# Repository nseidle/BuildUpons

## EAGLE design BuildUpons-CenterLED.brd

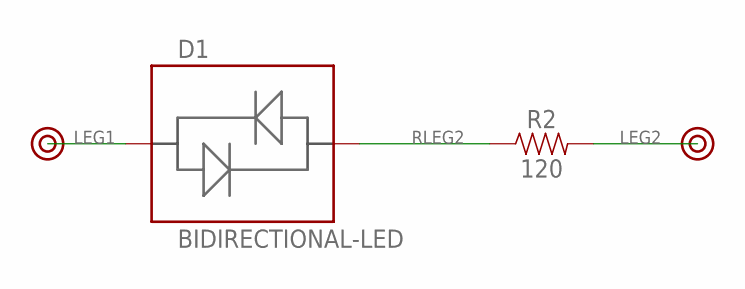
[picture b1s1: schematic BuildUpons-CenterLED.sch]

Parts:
D1: BIDIRECTIONAL-LED
J1, J2: METAL-LEGMOREPASTE; METAL-LEG
R2: 120; 0402

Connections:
LEG1: D1.LED1, J1.1
LEG2: J2.1, R2.2
RLEG2: D1.LED2, R2.1

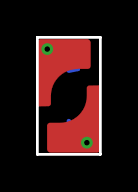
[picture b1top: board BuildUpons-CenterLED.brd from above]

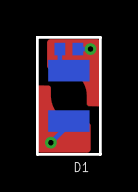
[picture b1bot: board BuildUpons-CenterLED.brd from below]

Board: 2 copper layers, 3.5 x 6.5 mm, 4 parts (2 on the bottom side), 3 nets.

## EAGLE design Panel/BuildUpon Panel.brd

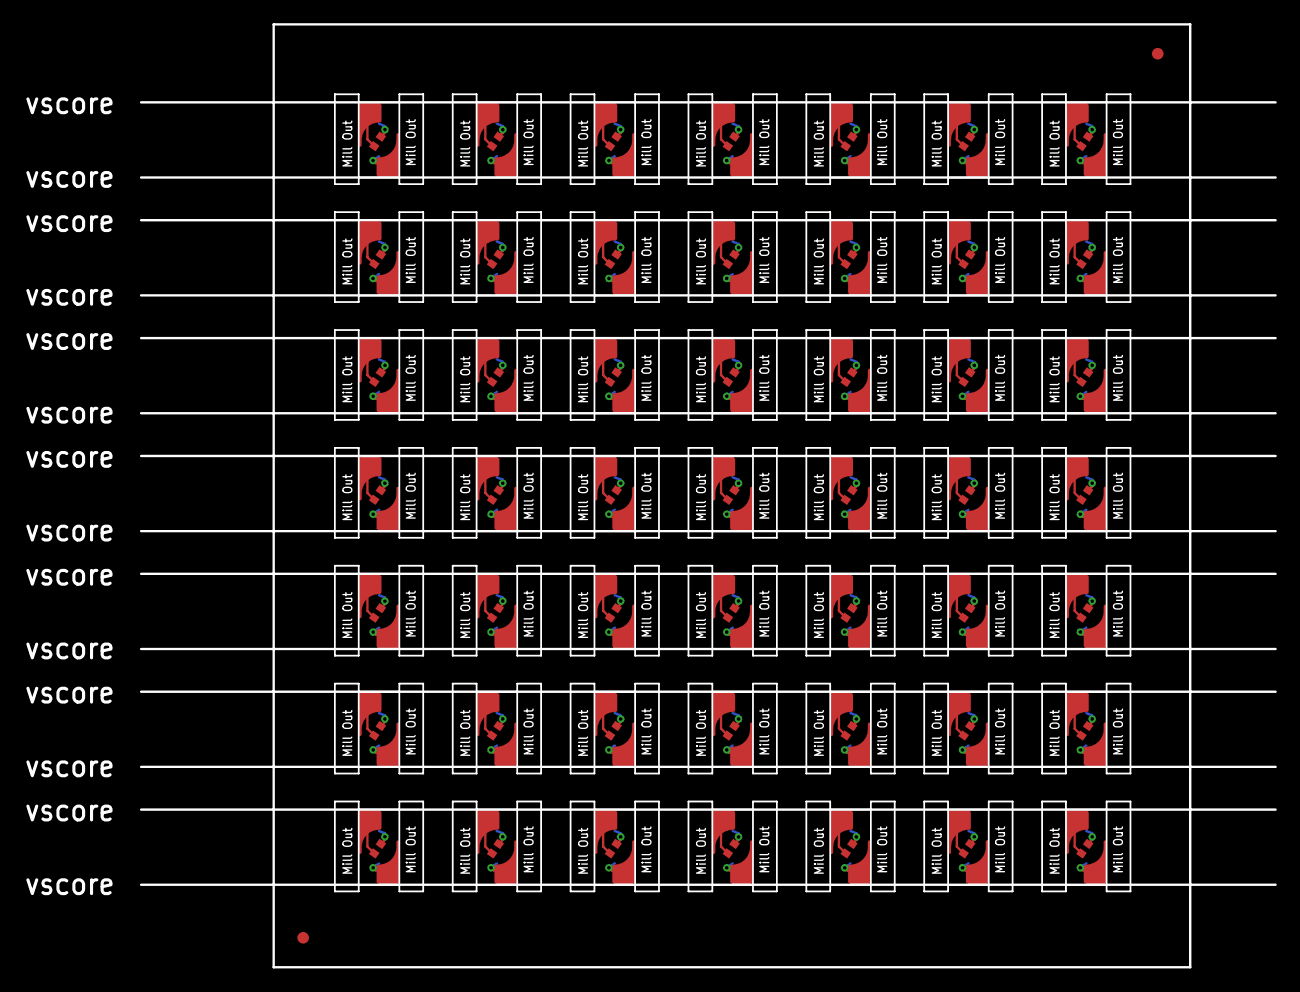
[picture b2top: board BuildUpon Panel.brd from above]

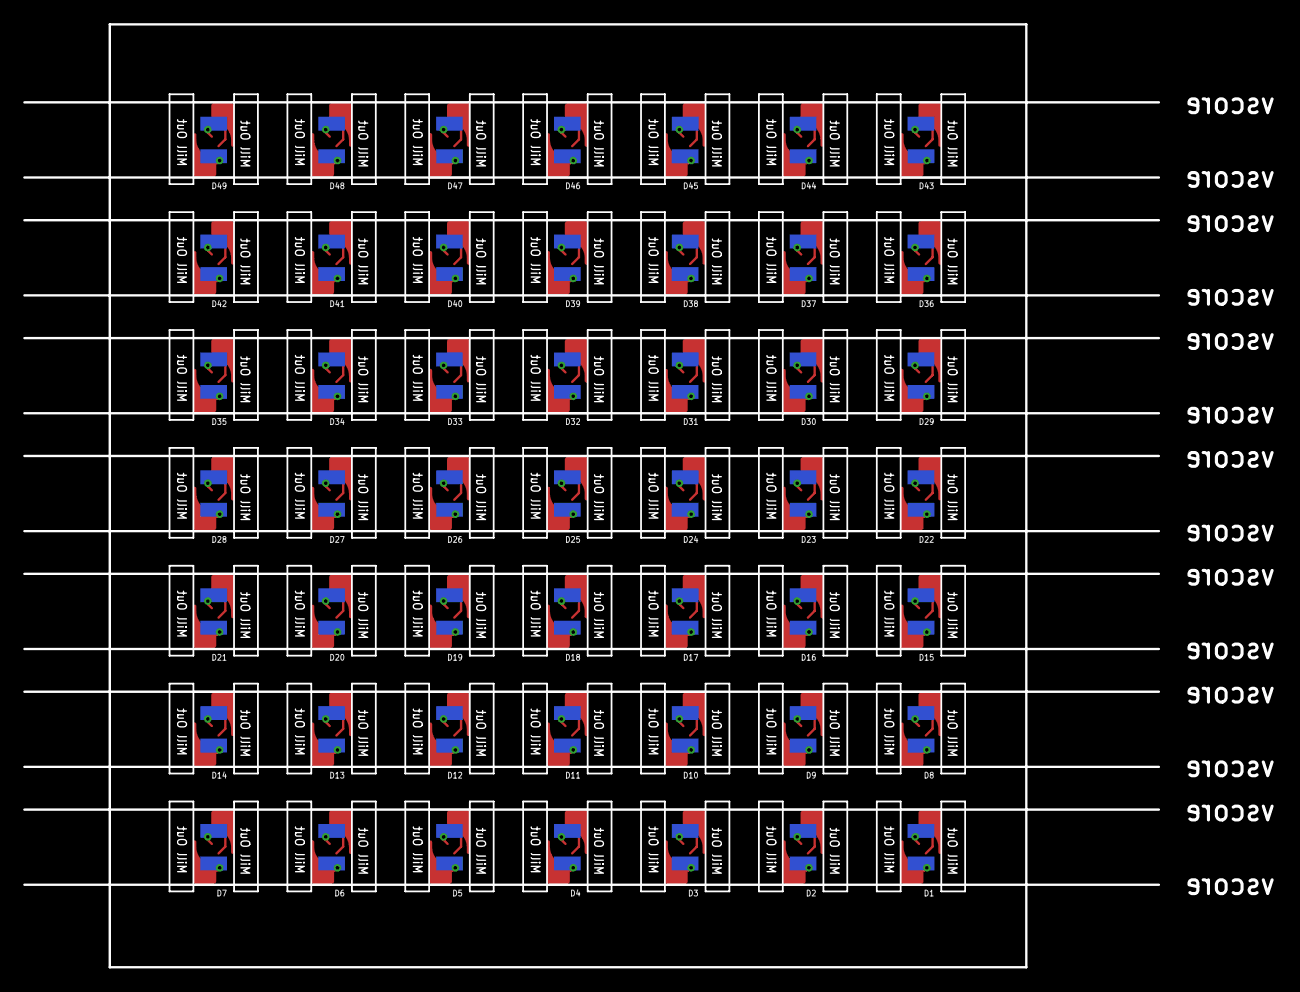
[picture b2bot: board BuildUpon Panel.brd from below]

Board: 2 copper layers, 107.8 x 81.3 mm, 198 parts (49 on the bottom side), 147 nets.

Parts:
D1, D2, D3, D4, D5, D6, D7, D8, D9, D10, D11, D12, D13, D14, D15, D16, D17, D18, D19, D20, D21, D22, D23, D24, D25, D26, D27, D28, D29, D30, D31, D32, D33, D34, D35, D36, D37, D38, D39, D40, D41, D42, D43, D44, D45, D46, D47, D48, D49: BIDIRECTIONAL-LED
E$1, E$2: FIDUCIAL-1X2
J1, J2, J3, J4, J5, J6, J7, J8, J9, J10, J11, J12, J13, J14, J15, J16, J17, J18, J19, J20, J21, J22, J23, J24, J25, J26, J27, J28, J29, J30, J31, J32, J33, J34, J35, J36, J37, J38, J39, J40, J41, J42, J43, J44, J45, J46, J47, J48, J49, J50, J51, J52, J53, J54, J55, J56, J57, J58, J59, J60, J61, J62, J63, J64, J65, J66, J67, J68, J69, J70, J71, J72, J73, J74, J75, J76, J77, J78, J79, J80, J81, J82, J83, J84, J85, J86, J87, J88, J89, J90, J91, J92, J93, J94, J95, J96, J97, J98: METAL-LEG; METAL-LEG-LESSPASTE
R1, R2, R3, R4, R5, R6, R7, R8, R9, R10, R11, R12, R13, R14, R15, R16, R17, R18, R19, R20, R21, R22, R23, R24, R25, R26, R27, R28, R29, R30, R31, R32, R33, R34, R35, R36, R37, R38, R39, R40, R41, R42, R43, R44, R45, R46, R47, R48, R49: 120; 0402

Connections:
LEG1: D1.LED1, J1.1
LEG2: J2.1, R2.2
LEG3: D2.LED1, J3.1
LEG4: J4.1, R1.2
LEG5: D3.LED1, J5.1
LEG6: J6.1, R3.2
LEG7: D4.LED1, J7.1
LEG8: J8.1, R4.2
LEG9: D5.LED1, J9.1
LEG10: J10.1, R5.2
LEG11: D6.LED1, J11.1
LEG12: J12.1, R6.2
LEG13: D7.LED1, J13.1
LEG14: J14.1, R7.2
LEG15: D8.LED1, J15.1
LEG16: J16.1, R8.2
LEG17: D9.LED1, J17.1
LEG18: J18.1, R9.2
LEG19: D10.LED1, J19.1
LEG20: J20.1, R10.2
LEG21: D11.LED1, J21.1
LEG22: J22.1, R11.2
LEG23: D12.LED1, J23.1
LEG24: J24.1, R12.2
LEG25: D13.LED1, J25.1
LEG26: J26.1, R13.2
LEG27: D14.LED1, J27.1
LEG28: J28.1, R14.2
LEG29: D15.LED1, J29.1
LEG30: J30.1, R15.2
LEG31: D16.LED1, J31.1
LEG32: J32.1, R16.2
LEG33: D17.LED1, J33.1
LEG34: J34.1, R17.2
LEG35: D18.LED1, J35.1
LEG36: J36.1, R18.2
LEG37: D19.LED1, J37.1
LEG38: J38.1, R19.2
LEG39: D20.LED1, J39.1
LEG40: J40.1, R20.2
LEG41: D21.LED1, J41.1
LEG42: J42.1, R21.2
LEG43: D22.LED1, J43.1
LEG44: J44.1, R22.2
LEG45: D23.LED1, J45.1
LEG46: J46.1, R23.2
LEG47: D24.LED1, J47.1
LEG48: J48.1, R24.2
LEG49: D25.LED1, J49.1
LEG50: J50.1, R25.2
LEG51: D26.LED1, J51.1
LEG52: J52.1, R26.2
LEG53: D27.LED1, J53.1
LEG54: J54.1, R27.2
LEG55: D28.LED1, J55.1
LEG56: J56.1, R28.2
LEG57: D29.LED1, J57.1
LEG58: J58.1, R29.2
LEG59: D30.LED1, J59.1
LEG60: J60.1, R30.2
LEG61: D31.LED1, J61.1
LEG62: J62.1, R31.2
LEG63: D32.LED1, J63.1
LEG64: J64.1, R32.2
LEG65: D33.LED1, J65.1
LEG66: J66.1, R33.2
LEG67: D34.LED1, J67.1
LEG68: J68.1, R34.2
LEG69: D35.LED1, J69.1
LEG70: J70.1, R35.2
LEG71: D36.LED1, J71.1
LEG72: J72.1, R36.2
LEG73: D37.LED1, J73.1
LEG74: J74.1, R37.2
LEG75: D38.LED1, J75.1
LEG76: J76.1, R38.2
LEG77: D39.LED1, J77.1
LEG78: J78.1, R39.2
LEG79: D40.LED1, J79.1
LEG80: J80.1, R40.2
LEG81: D41.LED1, J81.1
LEG82: J82.1, R41.2
LEG83: D42.LED1, J83.1
LEG84: J84.1, R42.2
LEG85: D43.LED1, J85.1
LEG86: J86.1, R43.2
LEG87: D44.LED1, J87.1
LEG88: J88.1, R44.2
LEG89: D45.LED1, J89.1
LEG90: J90.1, R45.2
LEG91: D46.LED1, J91.1
LEG92: J92.1, R46.2
LEG93: D47.LED1, J93.1
LEG94: J94.1, R47.2
LEG95: D48.LED1, J95.1
LEG96: J96.1, R48.2
LEG97: D49.LED1, J97.1
LEG98: J98.1, R49.2
RLEG1: D2.LED2, R1.1
RLEG2: D1.LED2, R2.1
RLEG3: D3.LED2, R3.1
RLEG4: D4.LED2, R4.1
RLEG5: D5.LED2, R5.1
RLEG6: D6.LED2, R6.1
RLEG7: D7.LED2, R7.1
RLEG8: D8.LED2, R8.1
RLEG9: D9.LED2, R9.1
RLEG10: D10.LED2, R10.1
RLEG11: D11.LED2, R11.1
RLEG12: D12.LED2, R12.1
RLEG13: D13.LED2, R13.1
RLEG14: D14.LED2, R14.1
RLEG15: D15.LED2, R15.1
RLEG16: D16.LED2, R16.1
RLEG17: D17.LED2, R17.1
RLEG18: D18.LED2, R18.1
RLEG19: D19.LED2, R19.1
RLEG20: D20.LED2, R20.1
RLEG21: D21.LED2, R21.1
RLEG22: D22.LED2, R22.1
RLEG23: D23.LED2, R23.1
RLEG24: D24.LED2, R24.1
RLEG25: D25.LED2, R25.1
RLEG26: D26.LED2, R26.1
RLEG27: D27.LED2, R27.1
RLEG28: D28.LED2, R28.1
RLEG29: D29.LED2, R29.1
RLEG30: D30.LED2, R30.1
RLEG31: D31.LED2, R31.1
RLEG32: D32.LED2, R32.1
RLEG33: D33.LED2, R33.1
RLEG34: D34.LED2, R34.1
RLEG35: D35.LED2, R35.1
RLEG36: D36.LED2, R36.1
RLEG37: D37.LED2, R37.1
RLEG38: D38.LED2, R38.1
RLEG39: D39.LED2, R39.1
RLEG40: D40.LED2, R40.1
RLEG41: D41.LED2, R41.1
RLEG42: D42.LED2, R42.1
RLEG43: D43.LED2, R43.1
RLEG44: D44.LED2, R44.1
RLEG45: D45.LED2, R45.1
RLEG46: D46.LED2, R46.1
RLEG47: D47.LED2, R47.1
RLEG48: D48.LED2, R48.1
RLEG49: D49.LED2, R49.1

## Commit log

2017-09-26 :neckbeard: Added .gitattributes & .gitignore files
2017-10-04 First round PCBs ordered
2017-11-24 Running FR4 jig test
2017-11-24 FR4 Jig cut complete

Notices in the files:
parts and their libraries:
SparkFun-Aesthetics: Licensing: Creative Commons ShareAlike 4.0 International - https://creativecommons.org/licenses/by-sa/4.0
